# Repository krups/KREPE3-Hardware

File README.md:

# KREPE3-Hardware
PCB design files and documentation for the hardware used in the University of Kentucky's 2026 KRUPS ISS mission. Further information for each component is found in its respective folder.

### Hardware Folders
- [Low Power Data Logger](LPDataLogger)

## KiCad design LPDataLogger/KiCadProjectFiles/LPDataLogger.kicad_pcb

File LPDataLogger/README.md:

# LP-DataLogger
PCB design files and documentation for low power data-logger module for KREPE-3

### PCB Render

### Components
- [Raspberry Pi Pico 2 (4MB Flash)](https://datasheets.raspberrypi.com/pico/pico-2-datasheet.pdf)
- [FSM300 9-axis IMU module](https://www.mouser.com/datasheet/2/1480/FSM30x_Datasheet-3196253.pdf)
- [MCP9600 Thermocouple to digital converter](https://ww1.microchip.com/downloads/aemDocuments/documents/MSLD/ProductDocuments/DataSheets/MCP960X-L0X-RL0X-Thermocouple-EMF-to-Temperature-Converter-plus-minus-1-5-degrees-Celcius-Maximum-Accuracy-DS20005426.pdf)
- [Honeywell SSCSRNN015PA3A3 Pressure Sensor](https://mm.digikey.com/Volume0/opasdata/d220001/medias/docus/2157/ssc_series_DS.pdf)

### Pin Mapping
| Pico 2 GPIO Pin | Net Name |
| --- | --- |
| GPIO4 | I2C_SDA |
| GPIO5 | I2C_SCL |
| GPIO6 | FSM300_RESET |
| GPIO7 | HINTN |
| GPIO8 | UART_LOGGER_TO_MAIN |
| GPIO9 | UART_MAIN_TO_LOGGER |
| GPIO10 | SD_SPI_CLK |
| GPIO11 | SD_SPI_MOSI |
| GPIO12 | SD_SPI_MISO |
| GPIO13 | SD_SPI_CS |

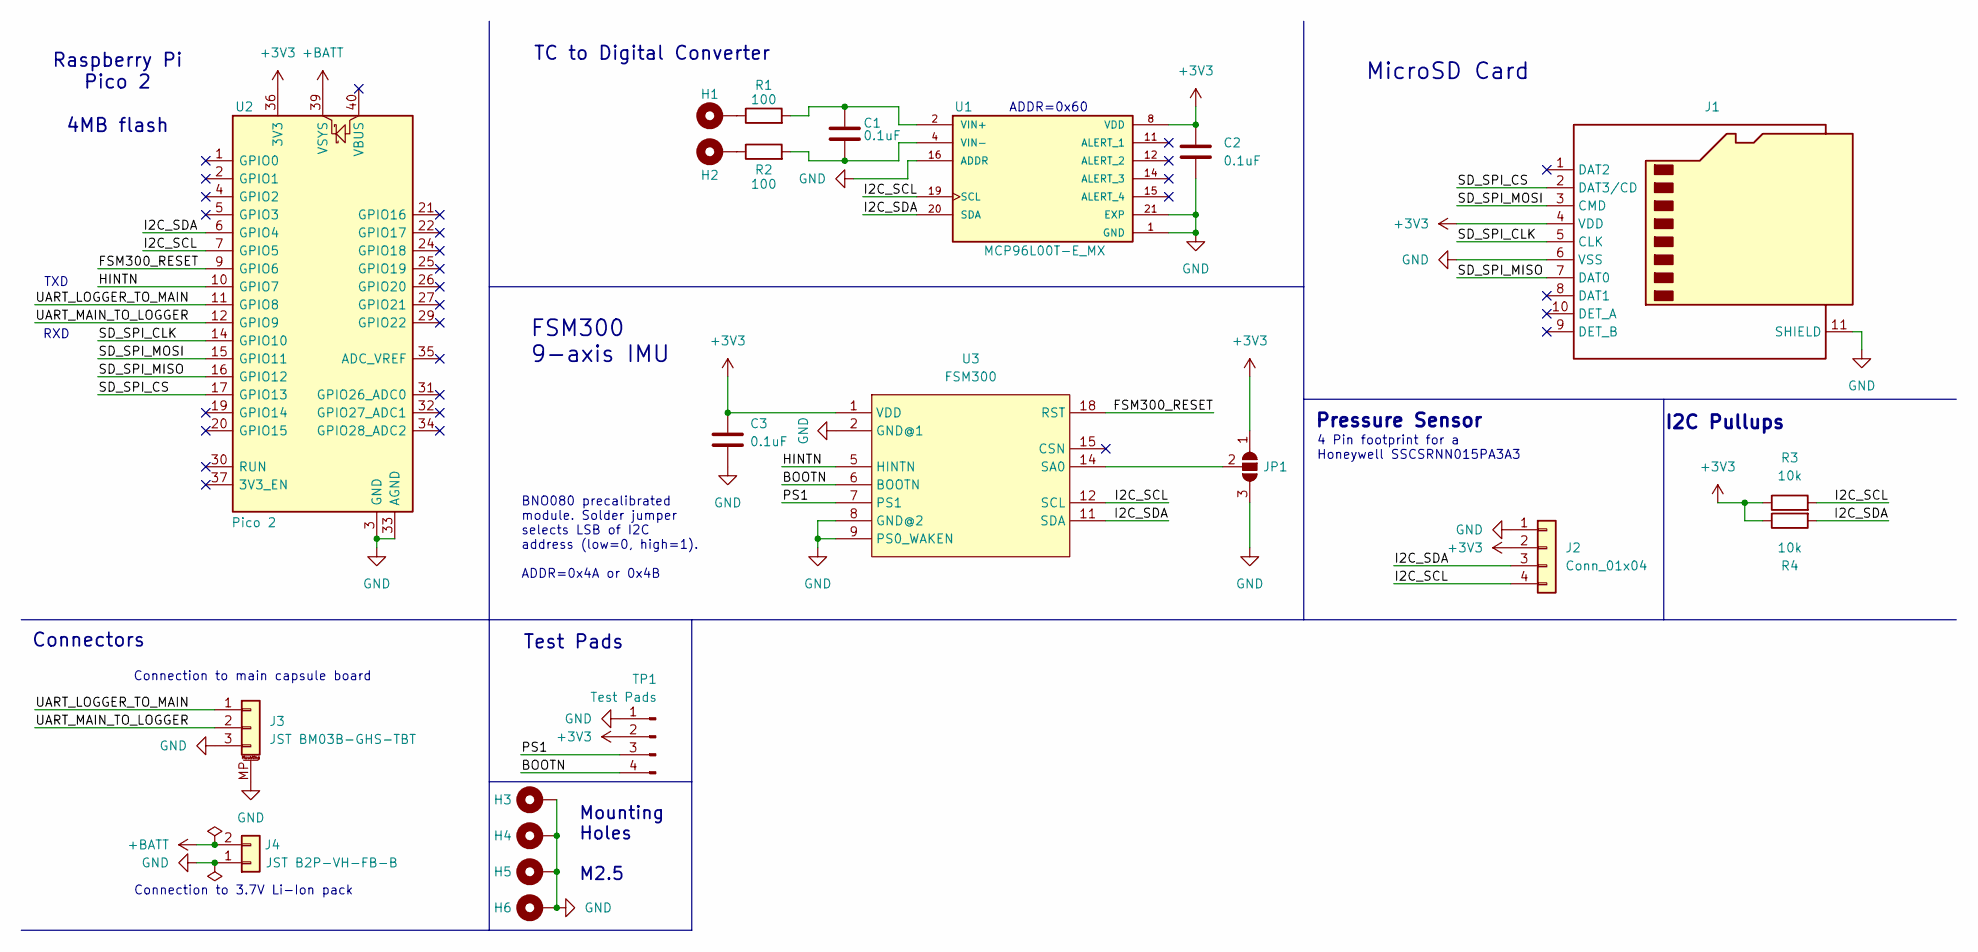
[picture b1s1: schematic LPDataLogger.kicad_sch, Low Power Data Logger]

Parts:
C1, C2, C3: 0.1uF; C_0603_1608Metric_Pad1.08x0.95mm_HandSolder; Digikey Part Number 0603B104K500XD
H1, H2: MountingHole_Pad; MountingHole_3.5mm_Pad
H3, H4, H5, H6: MountingHole_Pad; MountingHole_2.7mm_M2.5_Pad_with_stencil_hole
J1: Micro_SD_Card_Det2; microSD_HC_Molex_104031-0811; Digikey Part Number WM6357TR-ND
J2: Conn_01x04; PinHeader_1x04_P2.54mm_Vertical
J3: JST BM03B-GHS-TBT; JST_GH_BM03B-GHS-TBT_1x03-1MP_P1.25mm_Vertical; Digikey Part Number 455-BM03B-GHS-TBTCT-ND
J4: JST B2P-VH-FB-B; JST_VH_B2P-VH-FB-B_1x02_P3.96mm_Vertical; Digikey Part Number 455-B2P-VH-FB-B-ND
JP1: SolderJumper_3_Open; SolderJumper-3_P1.3mm_Open_RoundedPad1.0x1.5mm_NumberLabels
R1, R2: 100; R_0603_1608Metric_Pad0.98x0.95mm_HandSolder; Digikey Part Number 311-100GRTR-ND
R3, R4: 10k; R_0603_1608Metric_Pad0.98x0.95mm_HandSolder; Digikey Part Number 13-RC0603FR-1310KLTR-ND
TP1: Test Pads; PinHeader_2x02_P2.54mm_Vertical
U1: MCP96L00T-E_MX; QFN-20-1EP_5x5mm_P0.65mm_EP3.35x3.35mm; Digikey Part Number MCP96L00T-E/MXTR-ND
U2: Pico 2; RaspberryPi_Pico_Common_Unspecified; Digikey Part Number 2648-SC1631CT-ND
U3: FSM300; Digikey Part Number 1888-1001-ND

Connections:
+3V3: C2.1, C3.1, J1.4 (VDD), J2.2, JP1.1 (A), R3.1, R4.1, TP1.2, U1.8 (VDD), U2.36 (3V3), U3.1 (VDD)
+BATT: J4.2, U2.39 (VSYS)
/BOOTN: TP1.4, U3.6 (BOOTN)
/FSM300_RESET: U2.9 (GPIO6), U3.18 (RST)
/HINTN: U2.10 (GPIO7), U3.5 (HINTN)
/I2C_SCL: J2.4, R3.2, U1.19 (SCL), U2.7 (GPIO5), U3.12 (SCL)
/I2C_SDA: J2.3, R4.2, U1.20 (SDA), U2.6 (GPIO4), U3.11 (SDA)
/PS1: TP1.3, U3.7 (PS1)
/SD_SPI_CLK: J1.5 (CLK), U2.14 (GPIO10)
/SD_SPI_CS: J1.2 (DAT3/CD), U2.17 (GPIO13)
/SD_SPI_MISO: J1.7 (DAT0), U2.16 (GPIO12)
/SD_SPI_MOSI: J1.3 (CMD), U2.15 (GPIO11)
/UART_LOGGER_TO_MAIN: J3.1, U2.11 (GPIO8)
/UART_MAIN_TO_LOGGER: J3.2, U2.12 (GPIO9)
GND: C2.2, C3.2, H3.1, H4.1, H5.1, H6.1, J1.6 (VSS), J1.11 (SHIELD), J2.1, J3.3, J3.MP (MountPin), J4.1, JP1.3 (B), TP1.1, U1.1 (GND), U1.3 (GND__1), U1.5 (GND__2), U1.6 (GND__3), U1.7 (GND__4), U1.9 (GND__5), U1.10 (GND__6), U1.13 (GND__7), U1.16 (ADDR), U1.17 (GND__8), U1.18 (GND__9), U1.21 (EXP), U2.3 (GND), U2.8 (GND), U2.13 (GND), U2.18 (GND), U2.23 (GND), U2.28 (GND), U2.33 (AGND), U2.38 (GND), U3.2 (GND@1), U3.8 (GND@2), U3.9 (PS0_WAKEN)
unnamed: H1.1, R1.1
unnamed: H2.1, R2.1
unnamed: JP1.2 (C), U3.14 (SA0)
unnamed: C1.1, R1.2, U1.2 (VIN+)
unnamed: C1.2, R2.2, U1.4 (VIN-)

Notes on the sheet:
Connection to main capsule board
MicroSD Card
Mounting Holes M2.5
Connection to 3.7V Li-Ion pack
Test Pads
TC to Digital Converter
I2C Pullups
RXD
FSM300 9-axis IMU
TXD
Pressure Sensor
Connectors
ADDR=0x60
4 Pin footprint for a Honeywell SSCSRNN015PA3A3
BNO080 precalibrated module. Solder jumper selects LSB of I2C address (low=0, high=1). ADDR=0x4A or 0x4B
Raspberry Pi Pico 2 4MB flash

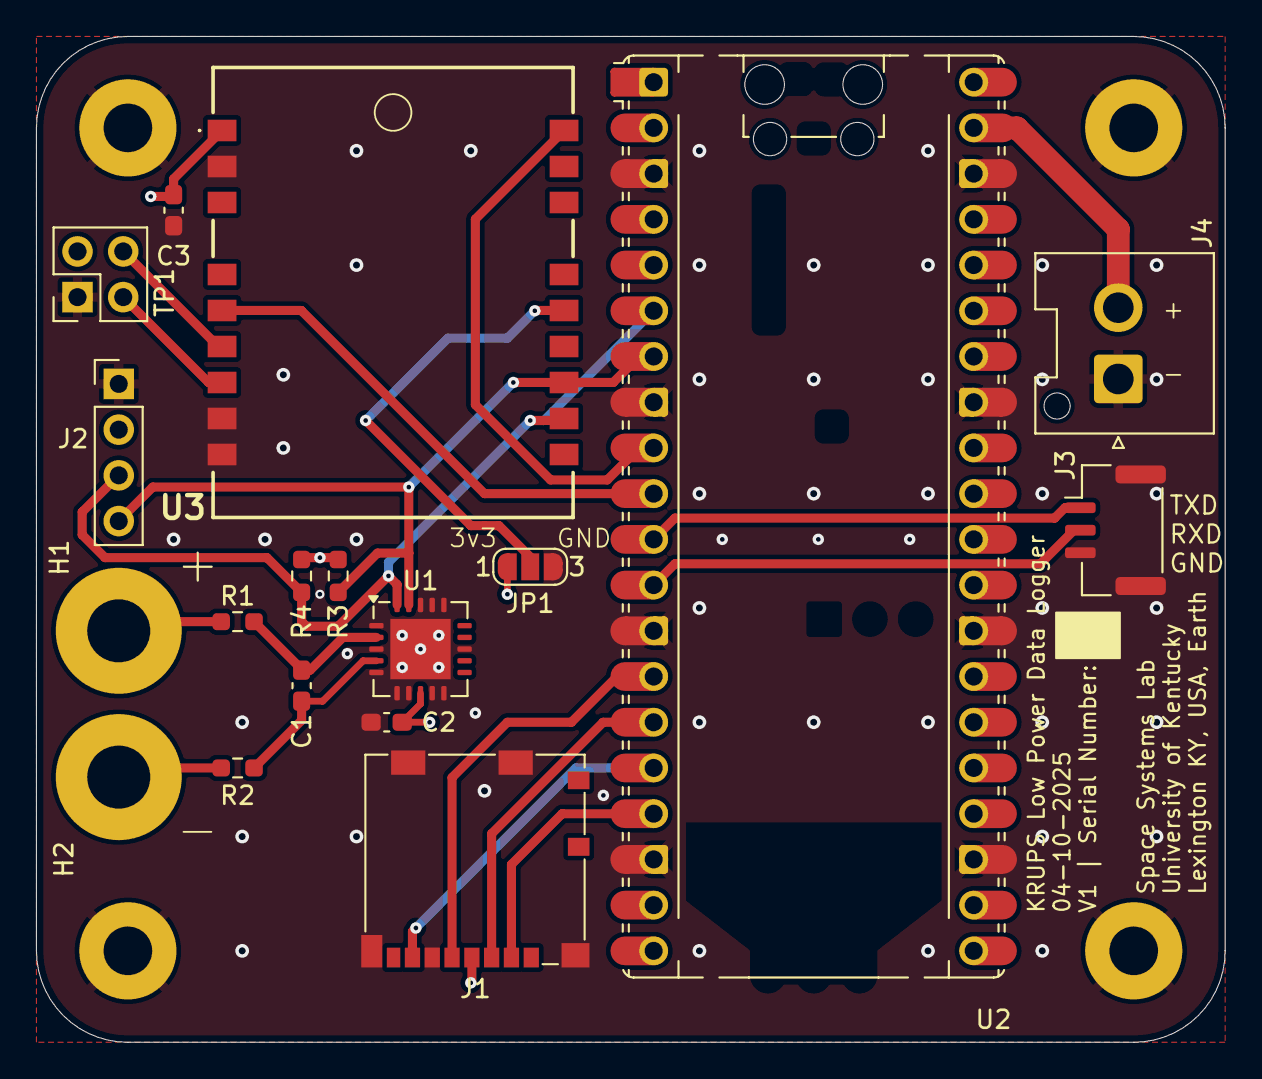
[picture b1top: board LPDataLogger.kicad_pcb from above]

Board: 4 copper layers, 66.0 x 55.9 mm, 22 parts (0 on the bottom side), 20 nets.

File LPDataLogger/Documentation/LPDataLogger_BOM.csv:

"Reference","Value","Qty","Digikey Part Number"
"C1,C2,C3","0.1uF","3","0603B104K500XD"
"J1","Micro_SD_Card_Det2","1","WM6357TR-ND"
"J3","JST BM03B-GHS-TBT","1","455-BM03B-GHS-TBTCT-ND"
"J4","JST B2P-VH-FB-B","1","455-B2P-VH-FB-B-ND"
"R1,R2","100","2","311-100GRTR-ND"
"R3,R4","10k","2","13-RC0603FR-1310KLTR-ND"
"U1","MCP96L00T-E_MX","1","MCP96L00T-E/MXTR-ND"
"U2","Pico 2","1","2648-SC1631CT-ND"
"U3","FSM300","1","1888-1001-ND"

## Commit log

2025-04-10 added gitignore
2025-04-10 finished first draft of low power data logger schematic
2025-04-10 fixed LPDL readme
2025-04-11 Finished V1 of the low power data logger
2025-04-11 added silkscreen, schematic labels for UART pins
2025-04-11 fixed LPDL BOM
